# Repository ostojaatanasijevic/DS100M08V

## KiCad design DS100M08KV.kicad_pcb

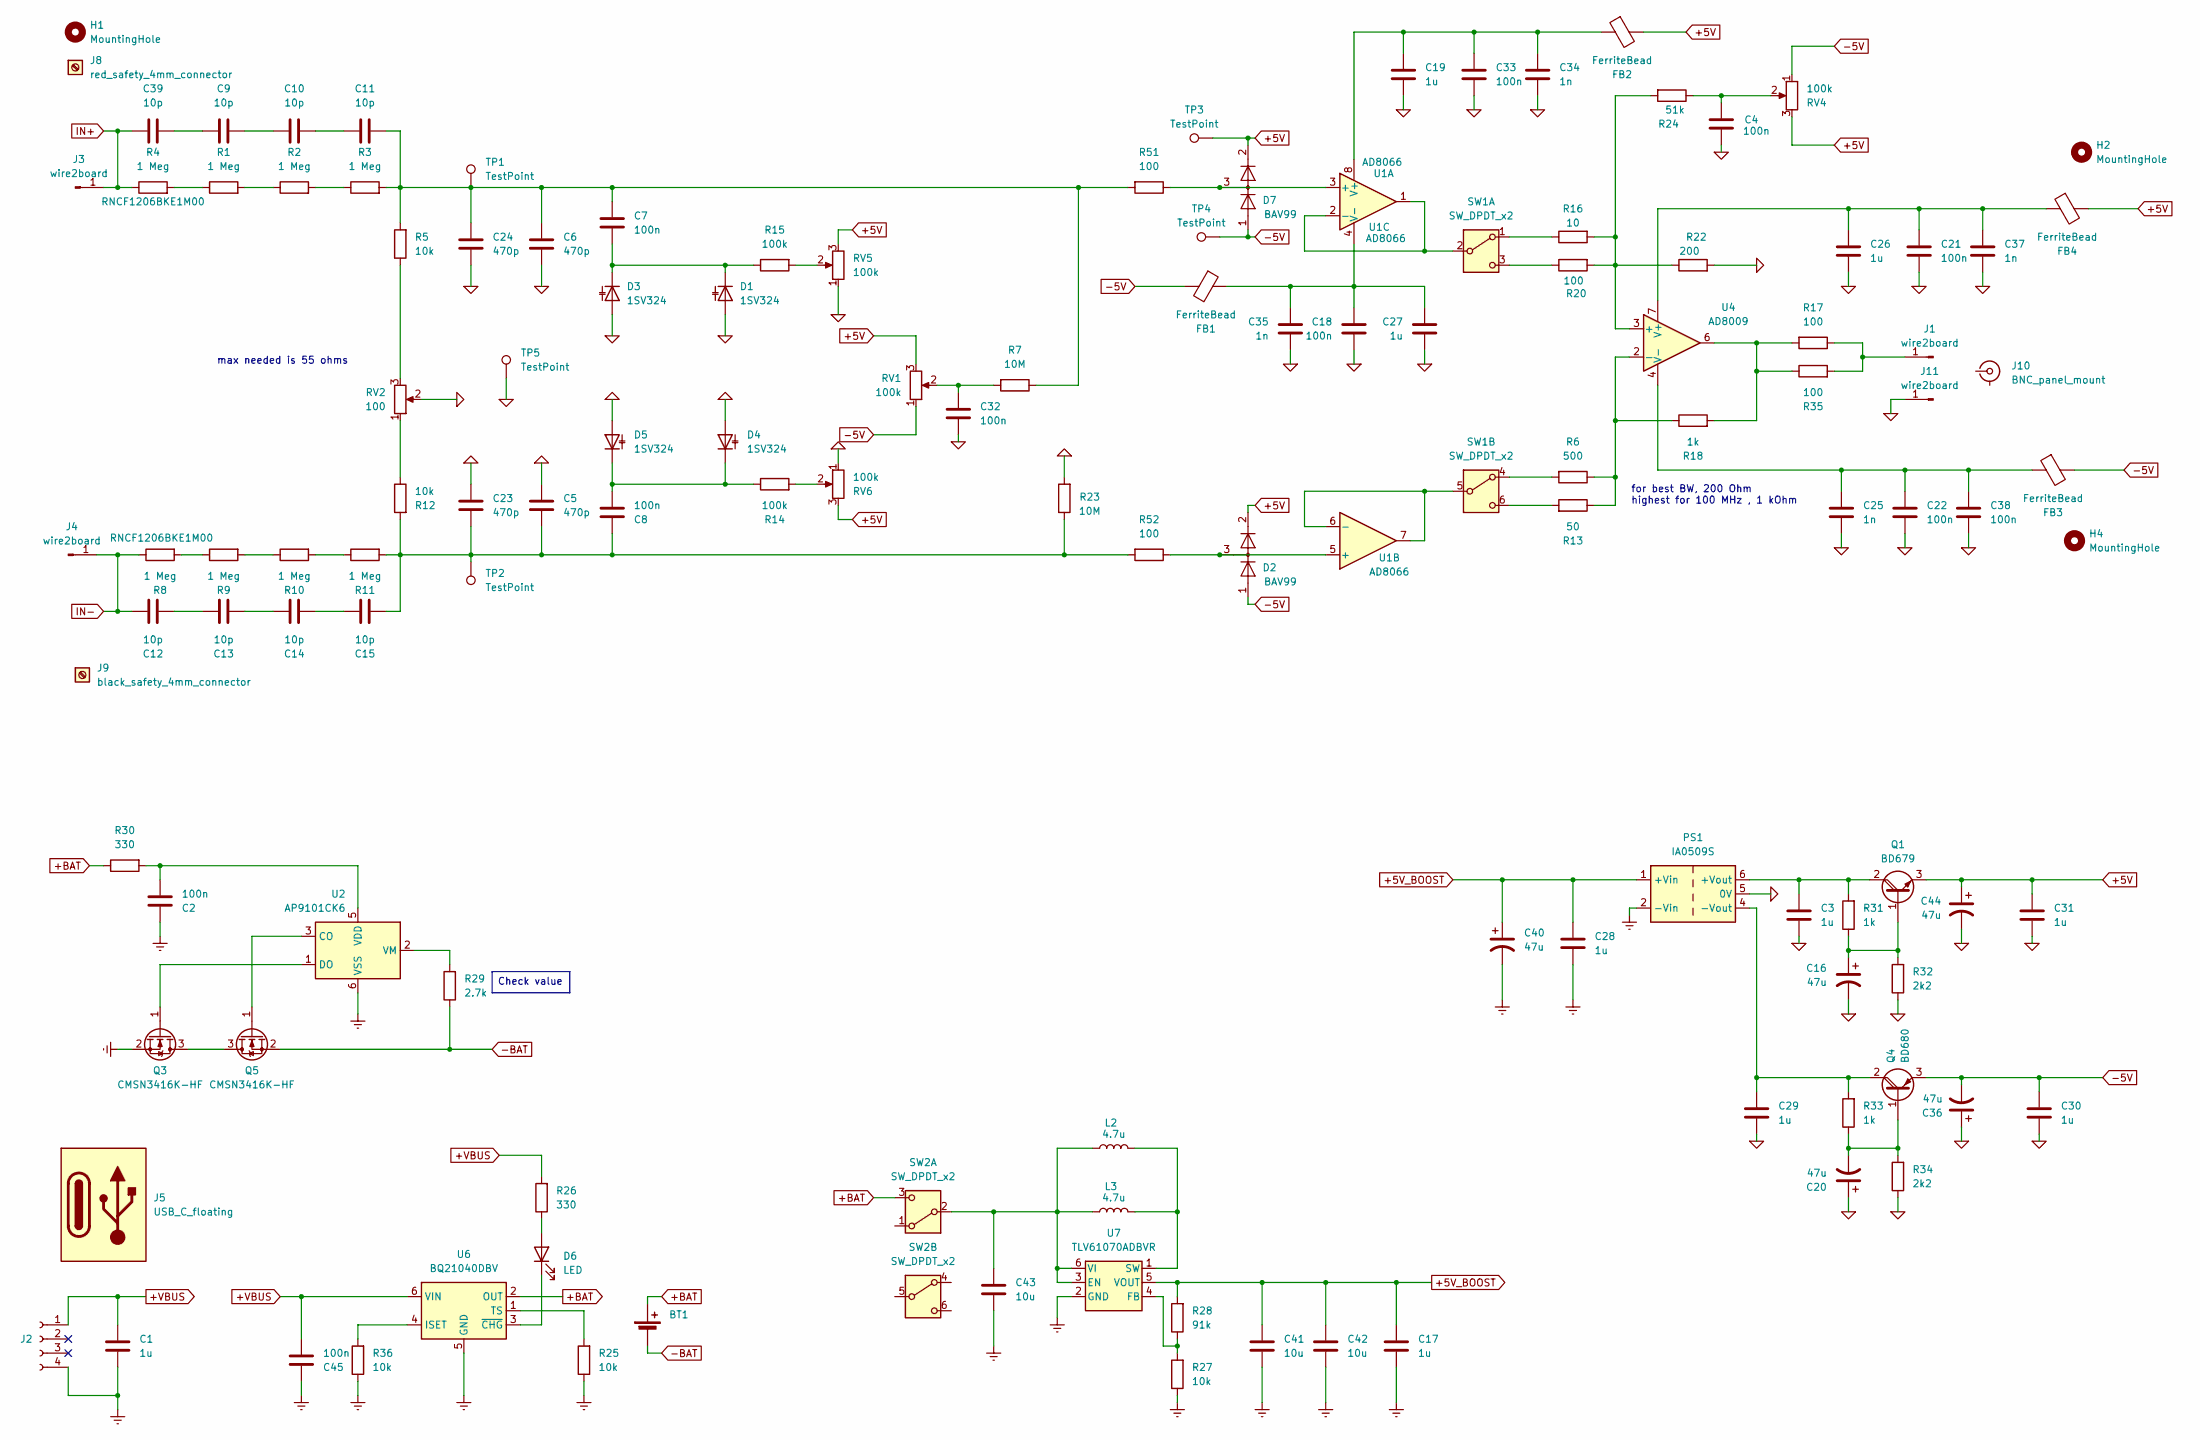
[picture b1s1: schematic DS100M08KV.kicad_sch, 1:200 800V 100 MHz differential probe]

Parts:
BT1: Battery_Cell; battery_holder
C1, C3, C17, C19, C26, C27, C28, C29, C30, C31: 1u; R_0603_1608Metric_Pad0.98x0.95mm_HandSolder
C2, C4, C7, C8, C18, C21, C22, C32, C33, C38, C45: 100n; R_0603_1608Metric_Pad0.98x0.95mm_HandSolder
C5, C6, C23, C24: 470p; R_0603_1608Metric_Pad0.98x0.95mm_HandSolder
C9, C10, C11, C12, C13, C14, C15, C39: 10p; R_1206_3216Metric_Pad1.30x1.75mm_HandSolder
C16, C20, C36, C40, C44: 47u; CP_Radial_D5.0mm_P2.00mm
C25, C34, C35, C37: 1n; R_0603_1608Metric_Pad0.98x0.95mm_HandSolder
C41, C42, C43: 10u; R_1206_3216Metric_Pad1.30x1.75mm_HandSolder
D1, D3, D4, D5: 1SV324; D_SOD-323_HandSoldering
D2, D7: BAV99; SOT-23
D6: LED; LED_D3.0mm_FlatTop
FB1, FB2, FB3, FB4: FerriteBead; L_0603_1608Metric_Pad1.05x0.95mm_HandSolder
H1, H2, H4: MountingHole; M3_with_screw
J1, J3, J4, J11: wire2board; SolderWire-0.25sqmm_1x01_D0.65mm_OD1.7mm
J2: Conn_01x04_Socket; JST_PH_B4B-PH-K_1x04_P2.00mm_Vertical
J5: USB_C_floating
J8: red_safety_4mm_connector; black_safety_4mm_connector
J9: black_safety_4mm_connector
J10: BNC_panel_mount
L2: 4.7u; L_Radial_D7.5mm_P3.50mm_Fastron_07P
L3: 4.7u; L_Bourns_SRN6045TA
PS1: IA0509S; Converter_DCDC_XP_POWER-IAxxxxS_THT
Q1: BD679; TO-126-3_Vertical
Q3, Q5: CMSN3416K-HF; SOT-23
Q4: BD680; TO-126-3_Vertical
R1, R2, R3, R9, R10, R11: 1 Meg; R_1206_3216Metric_Pad1.30x1.75mm_HandSolder
R4, R8: 1 Meg; R_1206_3216Metric_Pad1.30x1.75mm_HandSolder; Partnumber RNCF1206BKE1M00
R5, R12, R25, R27, R36: 10k; R_0603_1608Metric_Pad0.98x0.95mm_HandSolder
R6: 500; R_0603_1608Metric_Pad0.98x0.95mm_HandSolder
R7, R23: 10M; R_0603_1608Metric_Pad0.98x0.95mm_HandSolder
R13: 50; R_0603_1608Metric_Pad0.98x0.95mm_HandSolder
R14, R15: 100k; R_0603_1608Metric_Pad0.98x0.95mm_HandSolder
R16: 10; R_0603_1608Metric_Pad0.98x0.95mm_HandSolder
R17, R20, R35, R51, R52: 100; R_0603_1608Metric_Pad0.98x0.95mm_HandSolder
R18, R31, R33: 1k; R_0603_1608Metric_Pad0.98x0.95mm_HandSolder
R22: 200; R_0603_1608Metric_Pad0.98x0.95mm_HandSolder
R24: 51k; R_0603_1608Metric_Pad0.98x0.95mm_HandSolder
R26, R30: 330; R_0603_1608Metric_Pad0.98x0.95mm_HandSolder
R28: 91k; R_0603_1608Metric_Pad0.98x0.95mm_HandSolder
R29: 2.7k; R_0603_1608Metric_Pad0.98x0.95mm_HandSolder
R32, R34: 2k2; R_0603_1608Metric_Pad0.98x0.95mm_HandSolder
RV1, RV4, RV5, RV6: 100k; Potentiometer_Bourns_3296W_Vertical
RV2: 100; Potentiometer_Bourns_3296W_Vertical
SW1, SW2: SW_DPDT_x2; DPDT_bigger
TP1, TP2, TP3, TP4, TP5: TestPoint; TestPoint_Pad_D2.0mm
U1: AD8066; SOIC-8_3.9x4.9mm_P1.27mm
U2: AP9101CK6; SOT-23-6
U4: AD8009; SOIC-8_3.9x4.9mm_P1.27mm
U6: BQ21040DBV; SOT-23-6
U7: TLV61070ADBVR; SOT-23-6

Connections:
0: C3.2, C4.1, C5.1, C6.1, C16.2, C18.1, C19.1, C20.1, C21.1, C22.1, C23.1, C24.1, C25.1, C26.1, C27.1, C29.2, C30.2, C31.2, C32.1, C33.1, C34.1, C35.1, C36.1, C37.1, C38.1, C44.2, D1.2 (A), D3.2 (A), D4.2 (A), D5.2 (A), J11.1, PS1.5 (0V), R22.2, R23.2, R32.1, R34.1, RV2.2, RV5.1, RV6.1, TP5.1
+5V: C31.1, C44.1, D2.2 (A), D7.2 (A), FB2.2, FB4.2, Q1.3 (E), RV1.3, RV4.3, RV5.3, RV6.3, TP3.1
+5V_BOOST: C17.2, C28.1, C40.1, C41.2, C42.2, PS1.1 (+Vin), R28.2, U7.5 (VOUT)
+BAT: BT1.1 (+), R30.1, SW2.3 (C), U6.2 (OUT)
+VBUS: C1.1, C45.1, J2.1, R26.2, U6.6 (VIN)
-5V: C30.1, C36.2, D2.1 (K), D7.1 (K), FB1.2, FB3.2, Q4.3 (E), RV1.1, RV4.1, TP4.1
-BAT: BT1.2 (-), Q5.2 (S), R29.1
Earth: C1.2, C2.2, C17.1, C28.2, C40.2, C41.1, C42.1, C43.1, C45.2, J2.4, PS1.2 (-Vin), Q3.2 (S), R25.1, R27.1, R36.1, U2.6 (VSS), U6.5 (GND), U7.2 (GND)
IN+: C39.2, J3.1, R4.1
IN-: C12.2, J4.1, R8.1
unnamed: C4.2, R24.1, RV4.2
unnamed: C10.1, C11.2
unnamed: C9.1, C10.2
unnamed: C6.2, C7.2, C11.1, C24.2, R3.2, R5.2, R7.1, R51.2, TP1.1
unnamed: C12.1, C13.2
unnamed: C13.1, C14.2
unnamed: C14.1, C15.2
unnamed: C5.2, C8.2, C15.1, C23.2, R11.2, R12.2, R23.1, R52.2, TP2.1
unnamed: C32.2, R7.2, RV1.2
unnamed: C9.2, C39.1
unnamed: C7.1, D1.1 (K), D3.1 (K), R15.1
unnamed: C8.1, D4.1 (K), D5.1 (K), R14.1
unnamed: D6.2 (A), R26.1
unnamed: D6.1 (K), U6.3 (~CHG)
unnamed: J1.1, R17.1, R35.2
unnamed: C3.1, PS1.6 (+Vout), Q1.2 (C), R31.2
unnamed: C29.1, PS1.4 (-Vout), Q4.2 (C), R33.2
unnamed: C16.1, Q1.1 (B), R31.1, R32.2
unnamed: Q3.3 (D), Q5.3 (D)
unnamed: Q3.1 (G), U2.1 (DO)
unnamed: C20.2, Q4.1 (B), R33.1, R34.2
unnamed: Q5.1 (G), U2.3 (CO)
unnamed: R1.1, R4.2
unnamed: R1.2, R2.1
unnamed: R2.2, R3.1
unnamed: R5.1, RV2.3
unnamed: R8.2, R9.1
unnamed: R9.2, R10.1
unnamed: R10.2, R11.1
unnamed: R12.1, RV2.1
unnamed: R14.2, RV6.2
unnamed: R15.2, RV5.2
unnamed: R17.2, R18.2, R35.1, U4.6
unnamed: R16.1, SW1.1 (A)
unnamed: SW1.2 (B), U1.1, U1.2 (-)
unnamed: R20.1, SW1.3 (C)
unnamed: R6.2, SW1.4 (A)
unnamed: SW1.5 (B), U1.6 (-), U1.7
unnamed: R13.2, SW1.6 (C)
unnamed: C43.2, L2.1, L3.1, SW2.2 (B), U7.3 (EN), U7.6 (VI)
unnamed: D7.3 (K), R51.1, U1.3 (+)
unnamed: D2.3 (K), R52.1, U1.5 (+)
unnamed: C19.2, C33.2, C34.2, FB2.1, U1.8 (V+)
unnamed: C18.2, C27.2, C35.2, FB1.1, U1.4 (V-)
unnamed: C2.1, R30.2, U2.5 (VDD)
unnamed: R29.2, U2.2 (VM)
unnamed: R16.2, R20.2, R22.1, R24.2, U4.3 (+)
unnamed: R6.1, R13.1, R18.1, U4.2 (-)
unnamed: C21.2, C26.2, C37.2, FB4.1, U4.7 (V+)
unnamed: C22.2, C25.2, C38.2, FB3.1, U4.4 (V-)
unnamed: R36.2, U6.4 (ISET)
unnamed: R25.2, U6.1 (TS)
unnamed: R27.2, R28.1, U7.4 (FB)
unnamed: L2.2, L3.2, U7.1 (SW)

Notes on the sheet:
for best BW, 200 Ohm highest for 100 MHz , 1 kOhm
max needed is 55 ohms
Check value

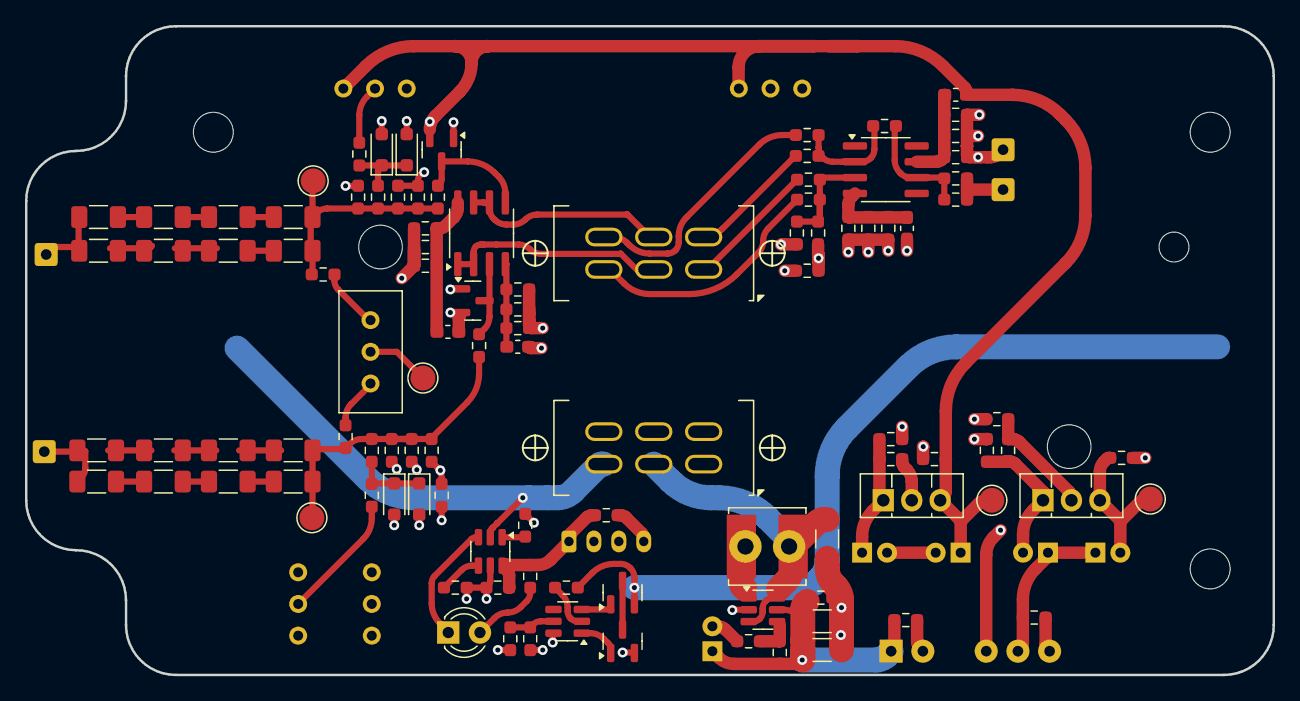
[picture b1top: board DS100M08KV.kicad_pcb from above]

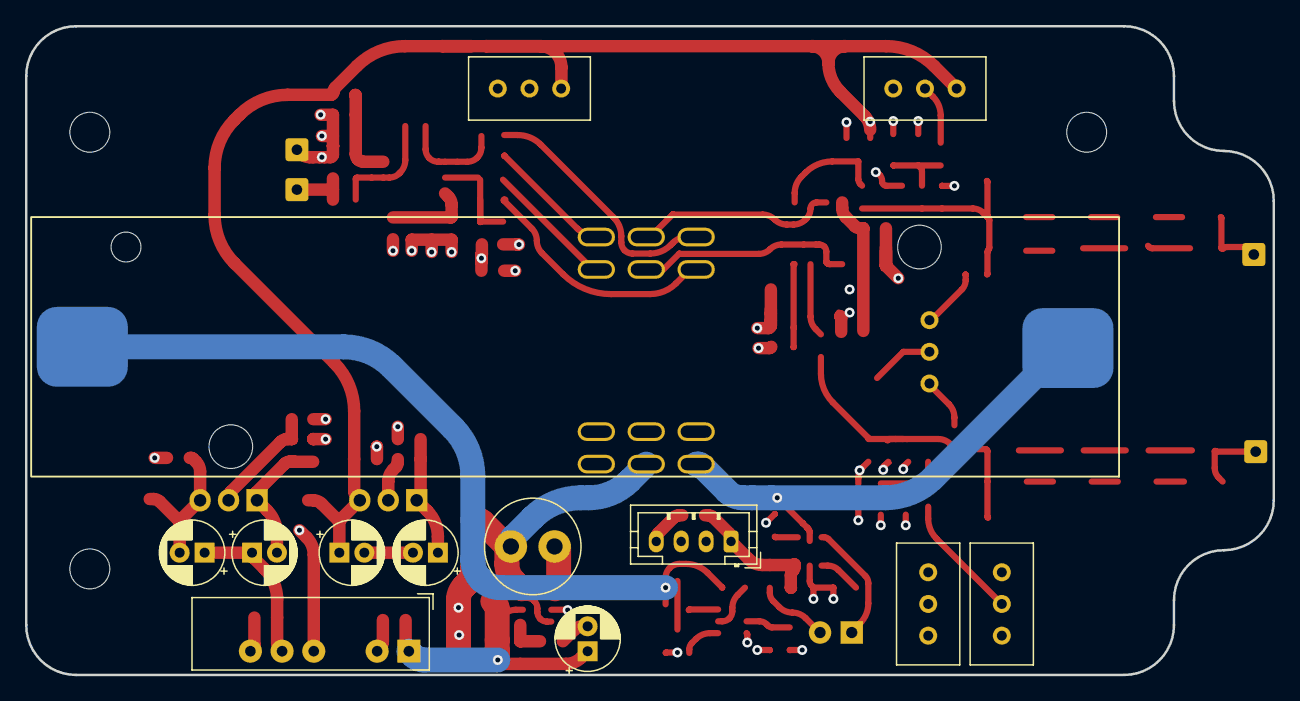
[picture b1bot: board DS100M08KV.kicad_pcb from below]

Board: 4 copper layers, 100.0 x 52.0 mm, 129 parts (20 on the bottom side), 64 nets.

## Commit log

2024-10-18 Uskoro sklanjamo buck-ove.
2024-10-18 Back to linear.
2024-10-19 Ill flip ya for it.
2024-10-20 Veći prekidač.
2024-10-20 Img tst
2024-10-20 Readme.
2024-10-20 dksjaf:
2024-10-20 Layout skoro gotov.
2024-10-20 Added PCB spacers.
2024-10-29 cap mult sim.
2024-10-29 Working on sims.
2024-10-29 Idk.
2024-10-29 Added capacitance multiplier.
2024-11-02 Fixed electrolytics.
2024-11-05 :wq:wq
2024-11-07 Ferrites.
2025-04-09 Project rename
2025-04-09 Cleaning up.
2025-04-09 Cleaning up libraries.
2025-04-09 Housekeeping.
2025-04-10 Clearer
2025-04-10 small updates.
2025-04-11 Novi raspored.
2025-04-13 Rutiranje.
2025-04-13 Rutiranje gotovo.
2025-04-13 README
2025-04-13 Minor update
2025-05-18 3d model.
2025-05-22 Rounded traces..
2025-10-20 Minor changes to schematic and PCB.
